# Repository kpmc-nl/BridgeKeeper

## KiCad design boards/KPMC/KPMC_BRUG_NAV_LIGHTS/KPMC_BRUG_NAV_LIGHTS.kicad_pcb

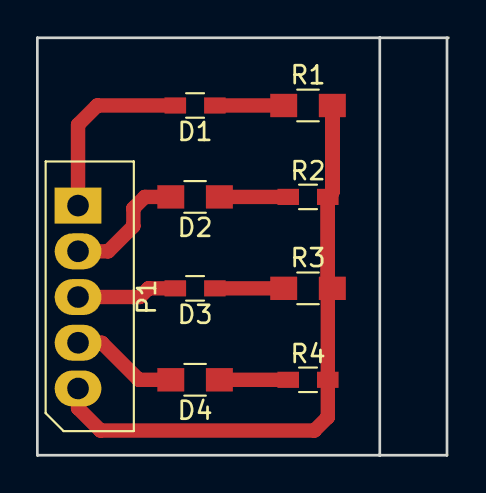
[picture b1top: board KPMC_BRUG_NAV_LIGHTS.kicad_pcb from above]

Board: 2 copper layers, 22.8 x 23.2 mm, 9 parts (0 on the bottom side), 9 nets.

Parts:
D1, D3: LED_R; R_0603_HandSoldering
D2, D4: LED_G; R_0805_HandSoldering
P1: CONN_01X05; Molex_SPOX-5267_22-03-5055_05x2.54mm_Straight
R1, R3: 100R; R_0805_HandSoldering
R2, R4: 60R; R_0603_HandSoldering

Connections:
unnamed: D1.1, R1.1
unnamed: D1.2, P1.1
unnamed: D2.1, R2.1
unnamed: D2.2, P1.2
unnamed: D3.1, R3.1
unnamed: D3.2, P1.3
unnamed: D4.1, R4.1
unnamed: D4.2, P1.4
unnamed: P1.5, R1.2, R2.2, R3.2, R4.2

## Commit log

2017-03-02 Arduino blink as cmake project
2017-03-02 Add example to flash with Arduino protocol
2017-03-02 It works!
2017-03-02 whut?
2017-03-31 Initial commit - trying out the Manchester protocol
2017-03-31 Add manchester src and initialize project
2017-03-31 aangepast
2017-04-01 took original code and modified to transmit Start, data, Stop bit
2017-04-01 changed original sourcefile and make it work
2017-04-21 proof of concept
2017-05-05 Write 4 pins in one call. Just trying some stuff...
2017-05-05 Working on attiny45 implementation... Not much luck ATM :(
2017-05-09 Move files from controller project to controller subdir
2017-05-09 Move files from lightpole project to lightpole subdir
2017-05-09 Merged bridge-controller and bridge-lightpole into a single repository with a multi-project cmake setup.
2017-05-12 Somewhat working lightpole impl.
2017-05-15 Got the 'protocol' working.
2017-05-15 Remove useless comments
2017-05-15 Move some stuff around in CMakeLists.txt so one can override the board type in the env.cmake file.
2017-05-17 Testing with the MPU6050 sensor
2017-05-17 Trying to make some sense from the output of the MPU6050
2017-05-18 Refine avr/cmake stuff a bit. Compiler optimization works now, too.
2017-05-18 Work around https://cmake.org/Bug/view.php?id=9985
2017-05-20 Some work on a remote controller.
2017-05-20 Use t841 for remote.
2017-05-21 Some more testing with the MPU6050
2017-05-21 Whoops, wrong DLPF mode
2017-05-21 Fix tiny841 upload issues on the Mac
2017-05-24 Testing up/down motion.
2017-05-24 Working prototype with both remote and actuator.
2017-05-26 Added "ease-in-out".
2017-06-23 Added files for board design.
2017-06-23 Revised directory structure in /boards dir
2017-06-28 Testing the integration of an MPU-6050 and an I2C LCD display in a single project.
2017-06-30 Added lib/LiquidCristal to git
2017-06-30 add display backlight blinky
2017-07-14 Add some sensible #defines for the pinout :)
2017-07-16 'digital' motor control, just to test...
2017-07-16 Fix include order of cmake files in lightpole/CMakeLists.txt
2017-07-18 [WIP] Began working on a more structured implementation.
2017-07-18 [WIP] Working on a more structured impl - hooked up the Receiver.
2017-07-19 [WIP] Working on a more structured impl - working on bridge actuator
2017-07-19 Brought back hacky thingy to test the navigation lights
2017-07-19 [WIP] Working on a more structured impl - mostly done bridge actuator.
2017-07-19 [WIP] Working on a more structured impl - bridge actuator done.
2017-07-21 Back to PWM'ing on FWD/BACK pins instead of ENABLE pin. It just seems to work better :)
2017-08-04 Remote: use new pinout
2017-08-18 cleanup
2017-08-18 Configurable up/down targets.
2017-10-11 Some last minute hacks from a month ago.
2018-02-14 Keep sending data as long as the buttons are pressed.
2018-02-21 Reworking the controller; remove buttons and display; introduced booster & idle state; PWM on motor enable pin instead of motor direction pin.
2018-02-22 Offload motor feedback to separate Attiny45.
2018-02-22 pinout for motorfb
2018-02-28 motor feedback works.
2018-03-03 Switch out motorfb board for a simple end stop.
2018-03-14 Enable all buttons.
2018-03-14 Introduce battery sensor & low battery compensation.
